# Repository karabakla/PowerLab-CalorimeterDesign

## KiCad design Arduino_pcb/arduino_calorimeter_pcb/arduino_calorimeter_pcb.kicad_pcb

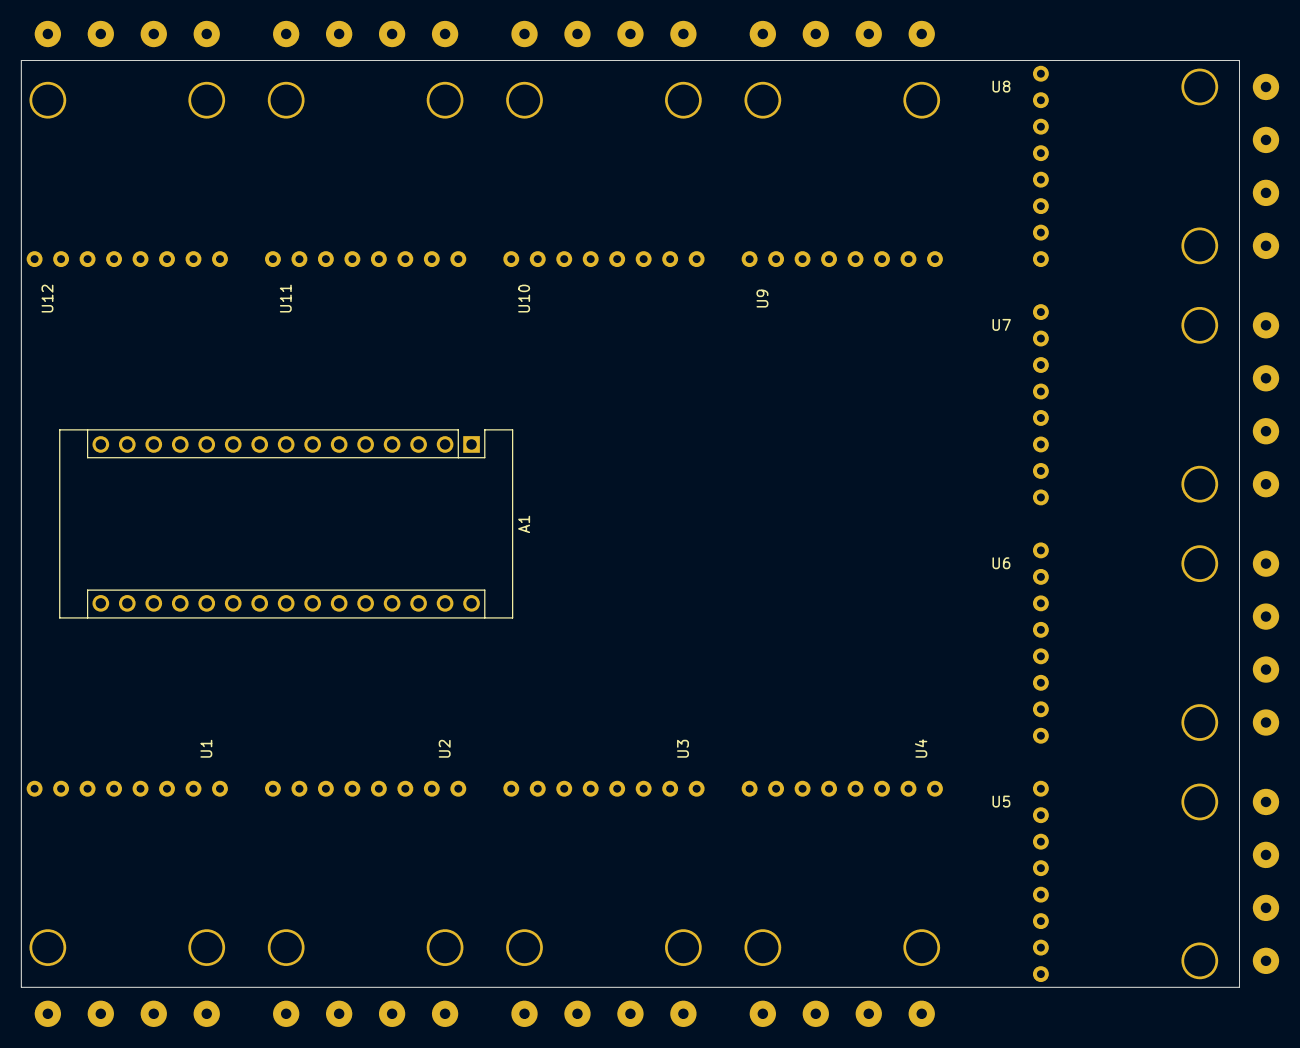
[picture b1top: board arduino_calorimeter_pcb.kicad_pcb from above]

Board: 2 copper layers, 116.8 x 88.9 mm, 13 parts (0 on the bottom side), 17 nets, no tracks yet.

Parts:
A1: Arduino_Nano_v3.x; Arduino_Nano
U1, U2, U3, U4, U5, U6, U7, U8, U9, U10, U11, U12: MAX31865_Module

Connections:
+5V: A1.27, U1.8, U2.8, U3.8, U4.8, U5.8, U6.8, U7.8, U8.8, U9.8, U10.8, U11.8, U12.8
CLK: A1.16, U1.3, U2.3, U3.3, U4.3, U5.3, U6.3, U7.3, U8.3, U9.3, U10.3, U11.3, U12.3
CS0: A1.5, U1.2
CS1: A1.6, U3.2
CS2: A1.7, U5.2
CS3: A1.8, U7.2
CS4: A1.9, U9.2
CS5: A1.10, U11.2
CS6: A1.11, U2.2
CS7: A1.12, U4.2
CS8: A1.13, U6.2
CS9: A1.19, U8.2
CS10: A1.20, U10.2
CS11: A1.21, U12.2
GND: A1.4, A1.29, U1.7, U2.7, U3.7, U4.7, U5.7, U6.7, U7.7, U8.7, U9.7, U10.7, U11.7, U12.7
SDI: A1.14, U1.4, U2.4, U3.4, U4.4, U5.4, U6.4, U7.4, U8.4, U9.4, U10.4, U11.4, U12.4
SDO: A1.15, U1.1, U2.1, U3.1, U4.1, U5.1, U6.1, U7.1, U8.1, U9.1, U10.1, U11.1, U12.1

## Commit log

2019-10-24 Some Files
2019-10-24 Changed summary file
2019-11-20 Calculation of box temp.
2019-11-20 correction
2019-12-12 Measurament&Test
    A test setup used, temp. had been measured by a GUI tool and thermal con. of the box estimated. Further improment needed on the test setup.
2019-12-12 Matlab files for calculation
2020-01-04 Last measurements &report
2021-10-20 arduino board
